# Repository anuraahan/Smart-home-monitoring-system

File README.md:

Node designs along with PCB and Schematic files in Node folder 
Node 2 is a better design with seperate ENS160 and AHT21 sensors so temperature less affected by heat from ENS160 
The code may have to be adjusted to get the right temp offset 
Screen code is an 2.8 inch ESP32-S3 from freenove 
https://docs.freenove.com/projects/fnk0104/en/latest/

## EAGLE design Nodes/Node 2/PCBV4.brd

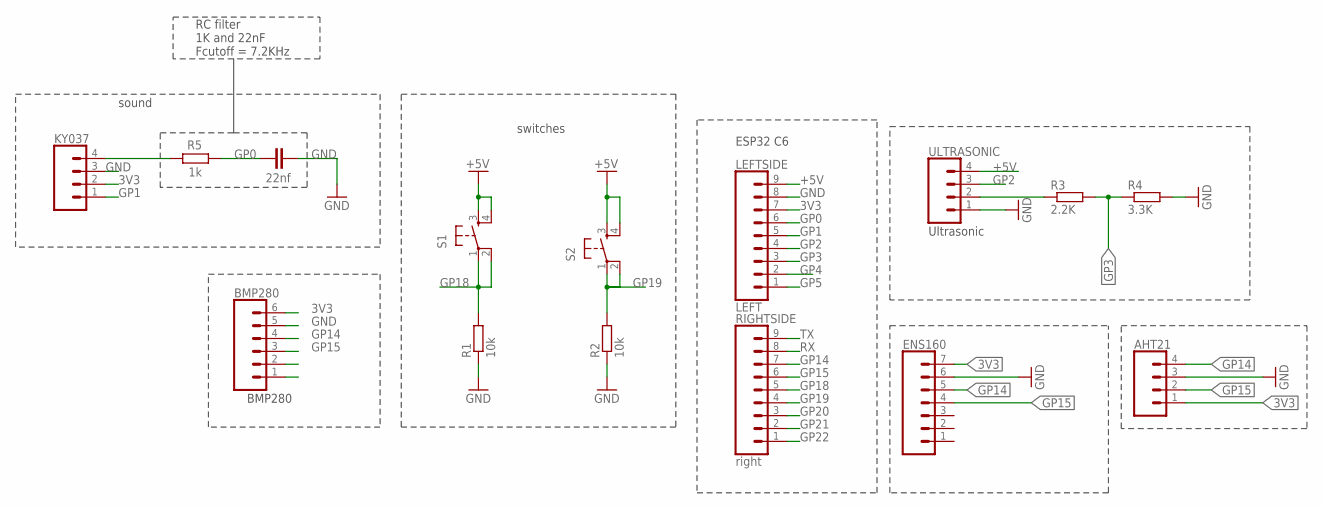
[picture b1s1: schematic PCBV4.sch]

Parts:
AHT21: CONN_04LONGPADS; 1X04_LONGPADS
BMP280: BMP280; SPARKFUN-CONNECTORS_1X06_LONGPADS
C1: 22nf; CAPACITOR-WIMA_C2.5-2
ENS160: CONN_07; 1X07
KY037: 1X04_SMD_STRAIGHT_COMBO; 1X04_LONGPADS
LEFTSIDE: LEFT; 1X09
R1, R2: 10k; 0207/10
R3: 2.2K; 0207/10
R4: 3.3K; 0207/10
R5: 1k; 0207/10
RIGHTSIDE: right; 1X09
S1, S2: EL311-ROBOT_SPARKFUN-ELECTROMECHANICAL_TAC_SWITCH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; EL311-ROBOT_SPARKFUN-ELECTROMECHANICAL_TACTILE-PTH
ULTRASONIC: 1X04_SMD_STRAIGHT_COMBO; 1X04_LONGPADS

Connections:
3V3: AHT21.1, BMP280.6, ENS160.7, KY037.2, LEFTSIDE.7
+5V: LEFTSIDE.9, S1.3, S1.4, S2.3, S2.4, ULTRASONIC.4
GND: AHT21.3, BMP280.5, C1.2, ENS160.6, KY037.3, LEFTSIDE.8, R1.1, R2.1, R4.2, ULTRASONIC.1
GP0: C1.1, LEFTSIDE.6, R5.1
GP1: KY037.1, LEFTSIDE.5
GP2: LEFTSIDE.4, ULTRASONIC.3
GP3: LEFTSIDE.3, R3.2, R4.1
GP4: LEFTSIDE.2
GP5: LEFTSIDE.1
GP14: AHT21.4, BMP280.4, ENS160.5, RIGHTSIDE.7
GP15: AHT21.2, BMP280.3, ENS160.4, RIGHTSIDE.6
GP18: R1.2, RIGHTSIDE.5, S1.1, S1.2
GP19: R2.2, RIGHTSIDE.4, S2.1, S2.2
GP20: RIGHTSIDE.3
GP21: RIGHTSIDE.2
GP22: RIGHTSIDE.1
unnamed: KY037.4, R5.2
unnamed: R3.1, ULTRASONIC.2
RX: RIGHTSIDE.8
TX: RIGHTSIDE.9

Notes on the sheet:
ESP32 C6
switches
Ultrasonic
BMP280
sound
RC filter 1K and 22nF Fcutoff = 7.2KHz

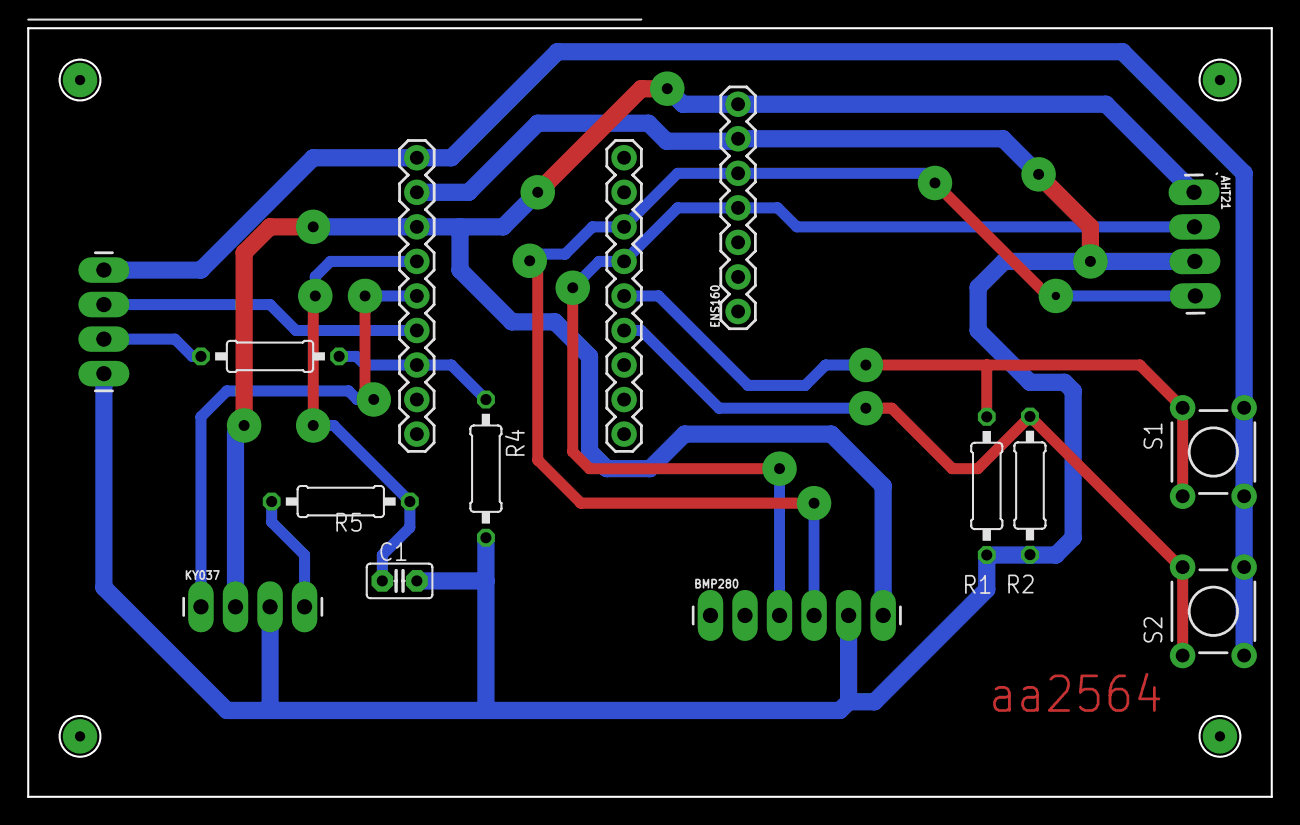
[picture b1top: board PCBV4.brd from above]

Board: 2 copper layers, 91.4 x 56.5 mm, 15 parts (0 on the bottom side), 13 nets.

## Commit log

2026-06-01 Codes for nodes
    Node2
2026-06-01 Node 1
2026-06-01 Main screen
2026-06-05 updated files

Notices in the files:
parts and their libraries:
SparkFun-Connectors: Licensing: Creative Commons ShareAlike 4.0 International - https://creativecommons.org/licenses/by-sa/4.0
